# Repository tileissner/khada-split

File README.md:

Released under CC BY-NC-SA 4.0 license

# khada-split
44 key ergo split

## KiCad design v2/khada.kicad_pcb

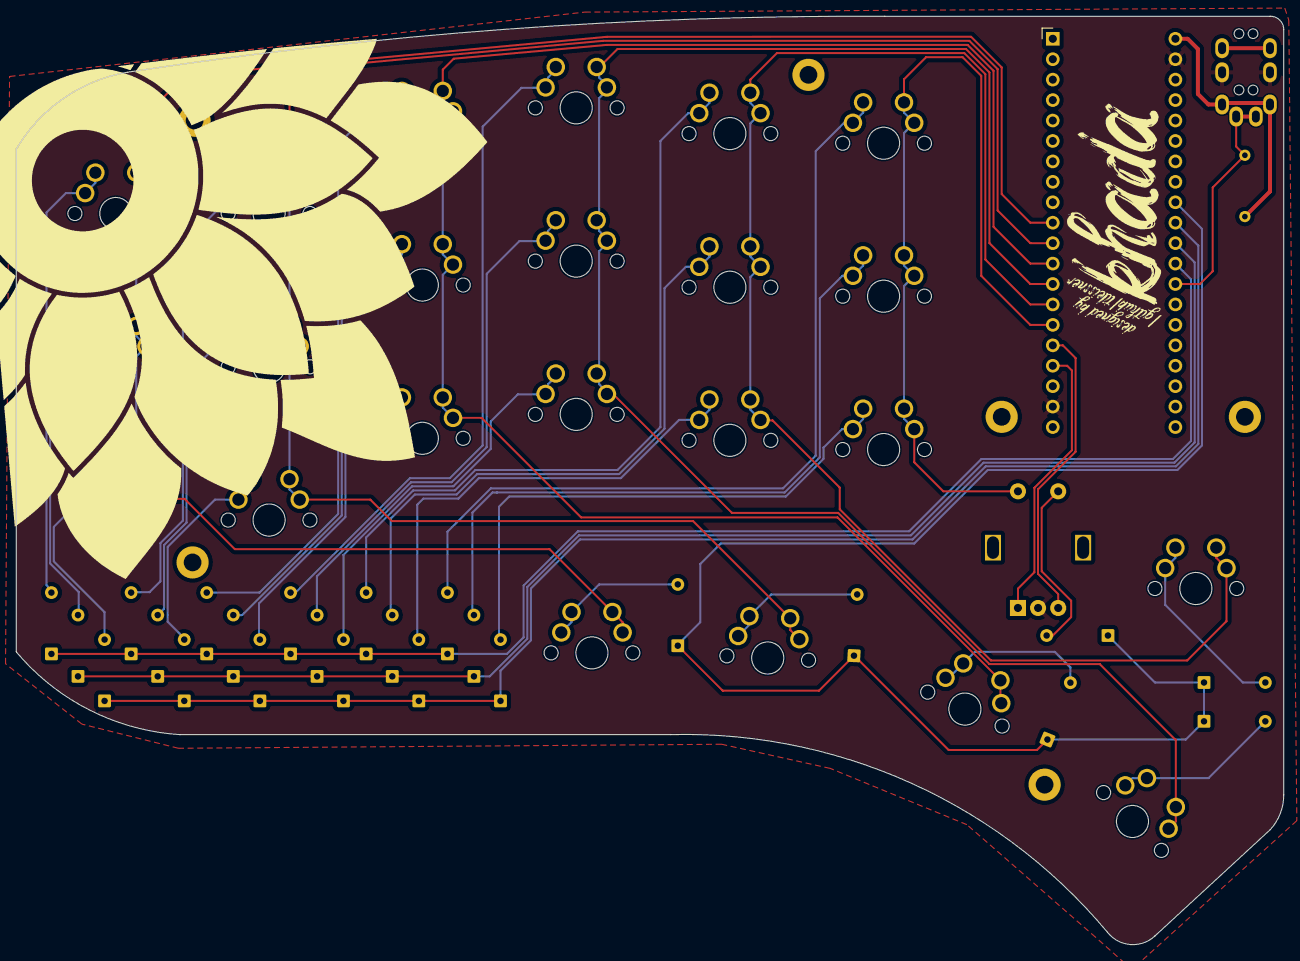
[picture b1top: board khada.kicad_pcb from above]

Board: 2 copper layers, 157.5 x 115.4 mm, 57 parts (0 on the bottom side), 39 nets.

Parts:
D1, D2, D3, D4, D5, D6, D7, D8, D9, D10, D11, D12, D13, D14, D15, D16, D17, D18, D19, D20, D21, D22, D23, D24: D_Small; D_THT_7.62mm_copy
H1, H2, H3, H4, H5, H6: Hole; M2_HOLE_PCB
J1: MJ-4PP-9
R1: 10k; R_Axial_DIN0204_L3.6mm_D1.6mm_P7.62mm_Horizontal
SW1, SW2, SW3, SW4, SW5, SW6, SW7, SW8, SW9, SW10, SW11, SW12, SW13, SW14, SW15, SW16, SW17, SW18, SW19, SW20, SW21, SW22, SW23: SW_Push; SW_MX_Reversible_1u_PadsOnBothLayers
SW24: RotaryEncoder_Switch; RotaryEncoder_Alps_EC11E-Switch_Vertical_H20mm
U1: YAAJ_WeAct_BlackPill_Part_Like_SWD_Breakout; YAAJ_WeAct_BlackPill_2_noSilk

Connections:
+5V: J1.D, R1.2, U1.40 (5V)
DATA: J1.A, R1.1, U1.28 (PA2)
GND: J1.C, SW24.C, U1.19 (GND), U1.39 (GND)
unnamed: D1.2 (A), SW1.1
unnamed: D2.2 (A), SW2.1
unnamed: D3.2 (A), SW3.1
unnamed: D4.2 (A), SW4.1
unnamed: D5.2 (A), SW5.1
unnamed: D6.2 (A), SW6.1
unnamed: D7.2 (A), SW7.1
unnamed: D8.2 (A), SW8.1
unnamed: D9.2 (A), SW9.1
unnamed: D10.2 (A), SW10.1
unnamed: D11.2 (A), SW11.1
unnamed: D12.2 (A), SW12.1
unnamed: D13.2 (A), SW13.1
unnamed: D14.2 (A), SW14.1
unnamed: D15.2 (A), SW15.1
unnamed: D16.2 (A), SW16.1
unnamed: D17.2 (A), SW17.1
unnamed: D18.2 (A), SW18.1
unnamed: D19.2 (A), SW19.1
unnamed: D20.2 (A), SW20.1
unnamed: D21.2 (A), SW21.1
unnamed: D22.2 (A), SW22.1
unnamed: D23.2 (A), SW23.1
unnamed: D24.2 (A), SW24.S1
ROTA: SW24.A, U1.17 (PB9)
ROTB: SW24.B, U1.16 (PB8)
col0: SW1.2, SW2.2, SW3.2, SW4.2, U1.10 (PA15)
col1: SW5.2, SW6.2, SW7.2, SW8.2, U1.11 (PB3)
col2: SW9.2, SW10.2, SW11.2, SW12.2, U1.12 (PB4)
col3: SW13.2, SW14.2, SW15.2, SW16.2, U1.13 (PB5)
col4: SW17.2, SW18.2, SW19.2, SW20.2, U1.14 (PB6)
col5: SW21.2, SW22.2, SW23.2, SW24.S2, U1.15 (PB7)
row0: D1.1 (K), D5.1 (K), D9.1 (K), D13.1 (K), D17.1 (K), D21.1 (K), U1.29 (PA3)
row1: D2.1 (K), D6.1 (K), D10.1 (K), D14.1 (K), D18.1 (K), D22.1 (K), U1.30 (PA4)
row2: D3.1 (K), D7.1 (K), D11.1 (K), D15.1 (K), D19.1 (K), D23.1 (K), U1.31 (PA5)
row3: D4.1 (K), D8.1 (K), D12.1 (K), D16.1 (K), D20.1 (K), D24.1 (K), U1.32 (PA6)

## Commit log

2021-11-22 1st commit
2021-11-23 cleaned up switch placement
2021-11-24 final design unless wiring incorrect
2021-11-26 added encoder
2021-12-01 edited switch footprint to have pads on both sides
2022-04-17 little clean up
2022-04-17 add FW
2022-04-18 add pcb images
2022-05-22 add v2 folder
2022-05-22 save before moving mcu out
2022-05-22 add new switch for macros
2022-05-22 new sw placement, new macro sw, trrs jack now on top
2022-06-04 add case folder
2022-06-05 case updated
2022-12-29 add firmware
